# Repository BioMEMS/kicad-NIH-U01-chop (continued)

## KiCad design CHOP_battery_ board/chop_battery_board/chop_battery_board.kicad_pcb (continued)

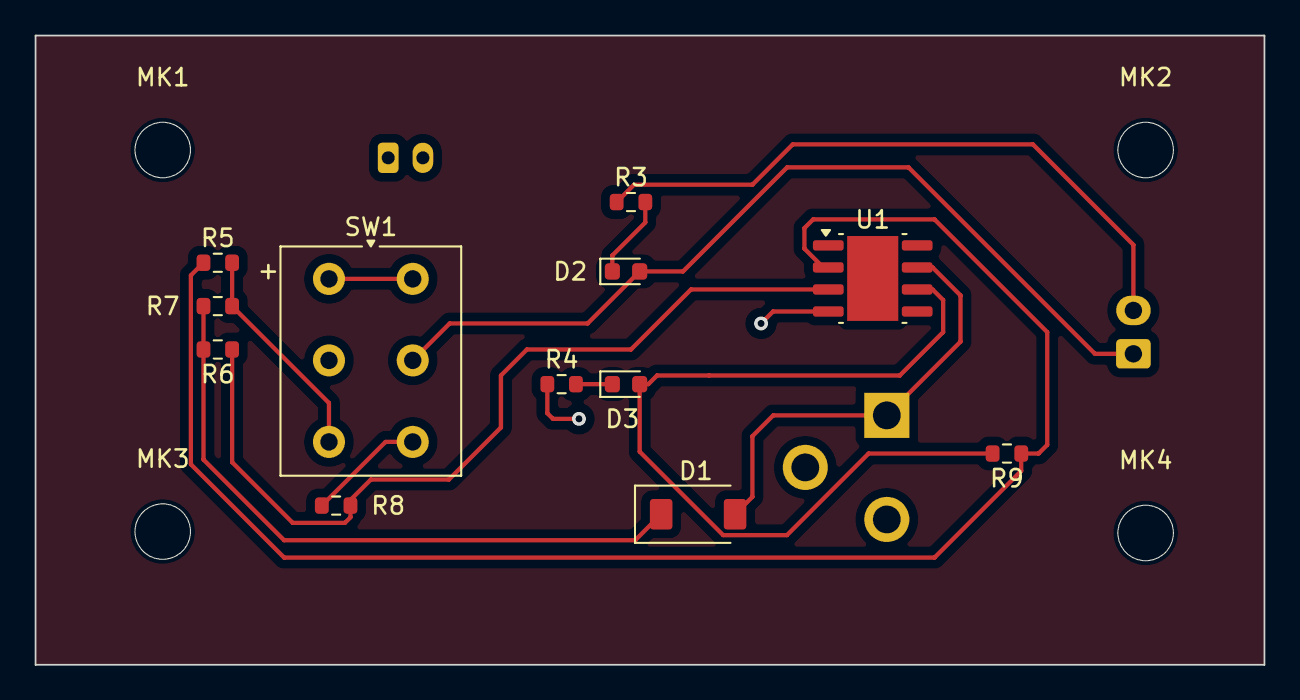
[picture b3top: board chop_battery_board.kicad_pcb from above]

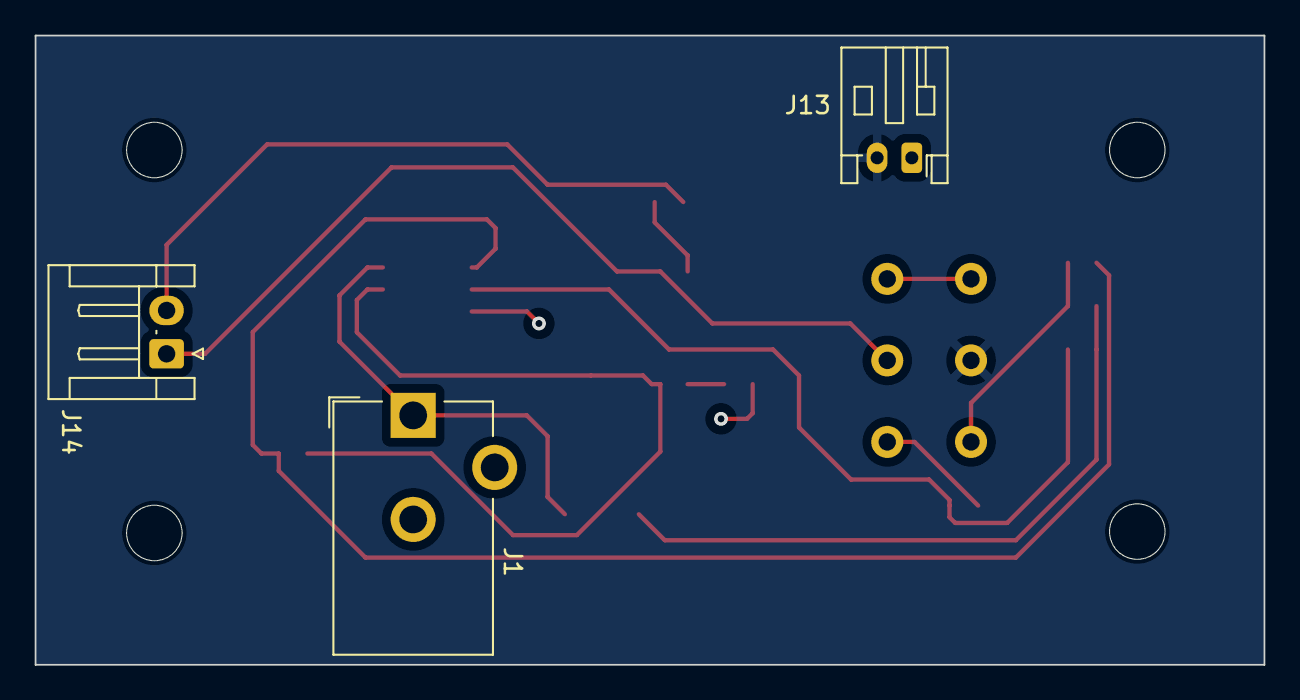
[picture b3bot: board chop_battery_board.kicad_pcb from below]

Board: 4 copper layers, 70.9 x 36.3 mm, 19 parts (3 on the bottom side), 12 nets.

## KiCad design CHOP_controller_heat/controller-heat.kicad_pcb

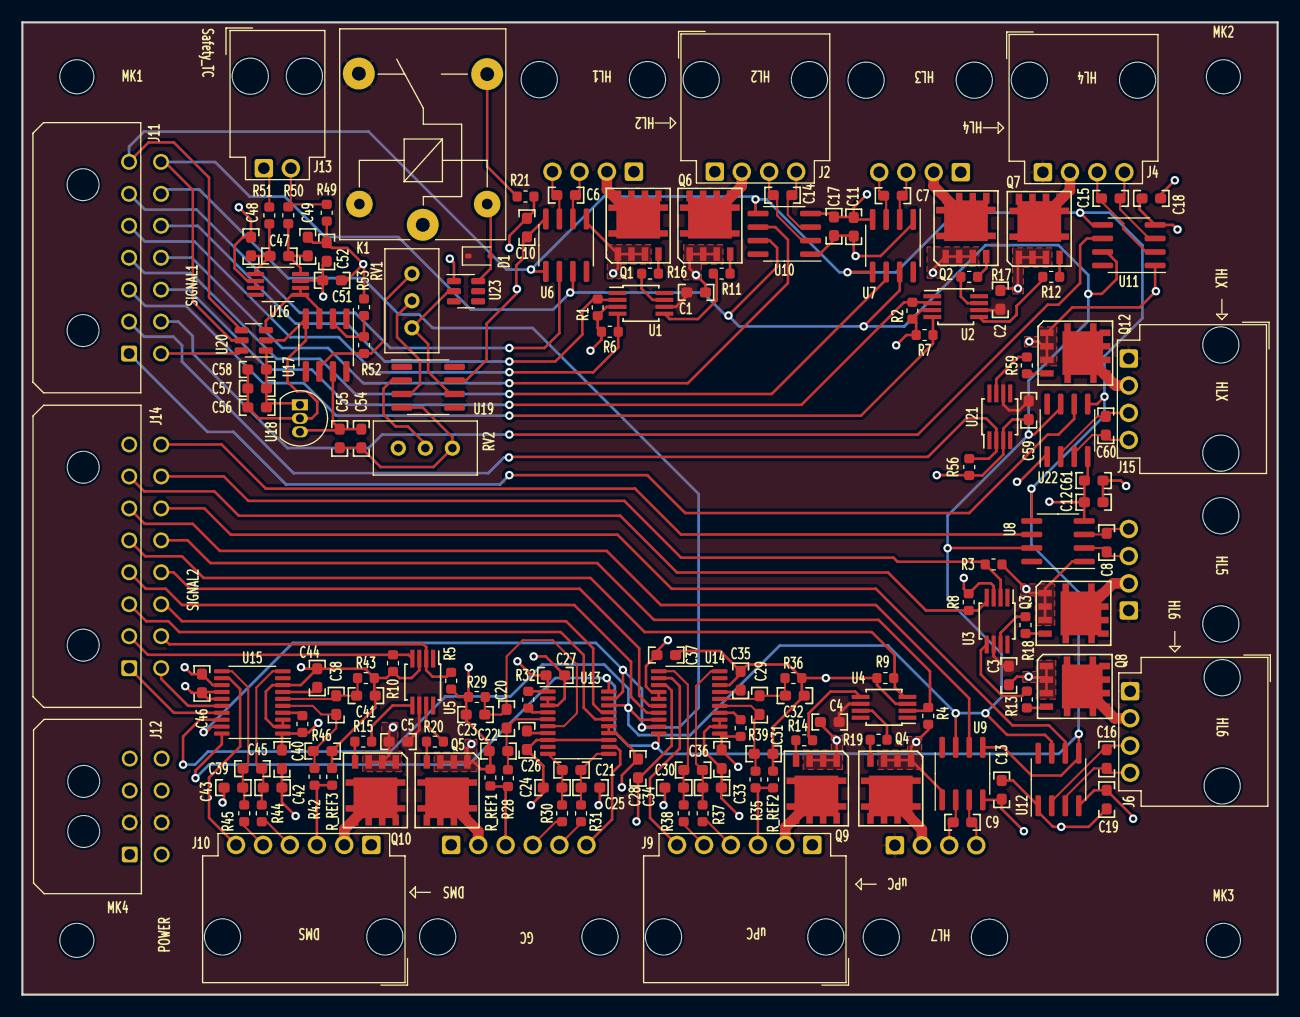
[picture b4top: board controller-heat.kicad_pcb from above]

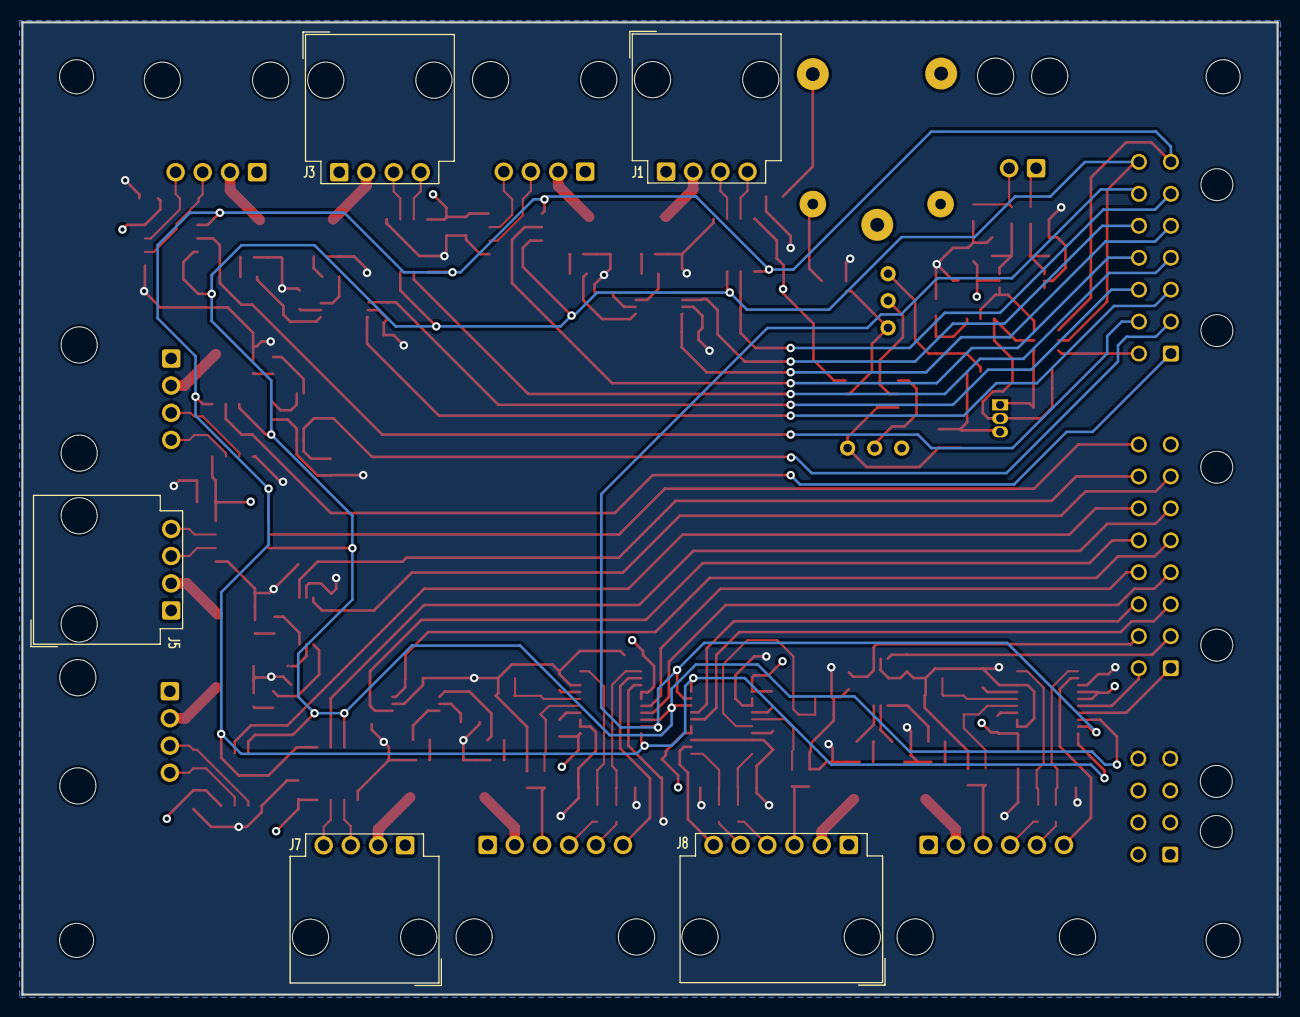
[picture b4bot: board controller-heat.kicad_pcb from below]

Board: 4 copper layers, 117.9 x 91.3 mm, 162 parts (5 on the bottom side), 126 nets.

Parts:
C1, C2, C3, C4, C5, C26, C35, C44, C59: 1u; C_0603_1608Metric_HandSolder
C6, C7, C8, C9, C14, C15, C16, C22, C23, C24, C25, C31, C32, C33, C34, C40, C41, C42, C43, C60: 10n; C_0603_1608Metric_HandSolder
C10, C11, C12, C13, C17, C18, C19, C20, C21, C27, C28, C29, C30, C36, C37, C38, C39, C45, C46, C61: 100n; C_0603_1608Metric_HandSolder
C47, C48, C49, C52, C54, C55: 10u; C_0603_1608Metric_HandSolder
C51, C56, C57, C58: 0.1u; C_0603_1608Metric_HandSolder
D1: BAT48JFILM; D_SOD-323
J1: HL1; Molex_SL_171975-0004_1x04_P2.54mm_Horizontal
J2: HL2; Molex_SL_171975-0004_1x04_P2.54mm_Horizontal
J3: HL3; Molex_SL_171975-0004_1x04_P2.54mm_Horizontal
J4: HL4; Molex_SL_171975-0004_1x04_P2.54mm_Horizontal
J5: HL5; Molex_SL_171975-0004_1x04_P2.54mm_Horizontal
J6: HL6; Molex_SL_171975-0004_1x04_P2.54mm_Horizontal
J7: HL7; Molex_SL_171975-0004_1x04_P2.54mm_Horizontal
J8: GC_RTD; Molex_SL_171975-0006_1x06_P2.54mm_Horizontal
J9: uPC_RTD; Molex_SL_171975-0006_1x06_P2.54mm_Horizontal
J10: DMS_RTD; Molex_SL_171975-0006_1x06_P2.54mm_Horizontal
J11: SIGNAL1; Molex_Micro-Fit_3.0_43045-1400_2x07_P3.00mm_Horizontal
J12: POWER; Molex_Micro-Fit_3.0_43045-0800_2x04_P3.00mm_Horizontal
J13: TC_SAFETY; Molex_SL_171975-0002_1x02_P2.54mm_Horizontal
J14: SIGNAL2; Molex_Micro-Fit_3.0_43045-1600_2x08_P3.00mm_Horizontal
J15: HLX; Molex_SL_171975-0004_1x04_P2.54mm_Horizontal
K1: J107F1CS1212VDC.36; Relay_SPDT_SANYOU_SRD_Series_Form_C
MK1, MK2, MK3, MK4: Mounting_Hole; MountingHole_3.2mm_M3
Q1, Q2, Q3, Q4, Q5, Q6, Q7, Q8, Q9, Q10, Q12: DMT6004LPS; PowerDI5060-8
R1, R2, R3, R4, R5, R6, R7, R8, R9, R10, R56: 4.7k; R_0603_1608Metric
R11, R12, R13, R14, R15, R16, R17, R18, R19, R20, R50, R51, R59: 100; R_0603_1608Metric
R21, R32, R39, R46: 10k; R_0603_1608Metric
R28, R29, R35, R36, R42, R43: 9.53k; R_0603_1608Metric
R30, R31, R37, R38, R44, R45: 10.5k; R_0603_1608Metric
R49: 1M; R_0603_1608Metric
R52: 9k; R_0603_1608Metric
R53: 1k; R_0603_1608Metric
RV1, RV2: 10k; Potentiometer_Bourns_3296W_Vertical
R_REF1, R_REF2, R_REF3: 2k; R_0603_1608Metric
U1, U2, U3, U4, U5, U21: TC4427; MSOP-8_3x3mm_P0.65mm_TI
U6, U7, U8, U9, U10, U11, U12, U22: MAX31855; SO-8_Maxim
U13, U14, U15: ADS1247; TSSOP-20_4.4x6.5mm_P0.65mm
U16: AD8497; MSOP-8_3x3mm_P0.65mm
U17, U19: LMC6081; SOIC-8_3.9x4.9mm_P1.27mm
U18: LP2950-3.3_TO92; TO-92_Inline
U20: ADC121S021; SOT-23-6
U23: NUD3124; SOT-23-6

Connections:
+3.3V: C10.1, C11.1, C12.1, C13.1, C17.1, C18.1, C19.1, C27.1, C28.1, C36.1, C37.1, C45.1, C46.1, C51.2, C52.2, C54.1, C55.1, C61.1, J12.3, J12.7, R32.1, R39.1, R46.1, RV2.1, U6.4 (VCC), U7.4 (VCC), U8.4 (VCC), U9.4 (VCC), U10.4 (VCC), U11.4 (VCC), U12.4 (VCC), U13.1 (DVDD), U13.14 (AVDD), U13.15 (Start), U14.1 (DVDD), U14.14 (AVDD), U14.15 (Start), U15.1 (DVDD), U15.14 (AVDD), U15.15 (Start), U16.7 (+Vs), U17.7 (V+), U18.3 (VI), U19.7 (V+), U22.4 (VCC)
+12V: C1.1, C2.1, C3.1, C4.1, C5.1, C59.1, D1.1 (K), J4.1, J5.1, J6.1, J7.1, J12.2, J12.6, J15.1, K1.4, K1.5, U1.6 (Vdd), U2.6 (Vdd), U3.6 (Vdd), U4.6 (Vdd), U5.6 (Vdd), U21.6 (Vdd)
+24V: J3.1, J8.1, J9.1, J10.1, J12.1, J12.5
/DMS_PWM_IN: J14.2, R10.1, U5.4 (IN_B)
/DMS_RTD+: J10.5, R45.2
/DMS_RTD++: J10.6, U15.12 (AIN3)
/DMS_RTD-: J10.4, R44.2
/DMS_RTD--: J10.3, R42.2, R_REF3.1
/DMS_RTD_CS: J14.9, U15.16 (N_CS)
/DMS_RTD_DRDY: J14.1, U15.17 (N_DRDY)
/GC_PWM_IN: J14.10, R5.1, U5.2 (IN_A)
/GC_RTD+: J8.5, R31.2
/GC_RTD++: J8.6, U13.12 (AIN3)
/GC_RTD-: J8.4, R30.2
/GC_RTD--: J8.3, R28.2, R_REF1.1
/GC_RTD_CS: J14.3, U13.16 (N_CS)
/GC_RTD_DRDY: J14.11, U13.17 (N_DRDY)
/HL1_CS: J11.6, U6.6 (N_CS)
/HL1_PWM_IN: J11.12, R1.1, U1.2 (IN_A)
/HL2_CS: J11.11, U10.6 (N_CS)
/HL2_PWM_IN: J11.5, R6.1, U1.4 (IN_B)
/HL3_CS: J11.4, U7.6 (N_CS)
/HL3_PWM_IN: J11.10, R2.1, U2.2 (IN_A)
/HL4_CS: J11.9, U11.6 (N_CS)
/HL4_PWM_IN: J11.3, R7.1, U2.4 (IN_B)
/HL5_CS: J14.16, U8.6 (N_CS)
/HL5_PWM_IN: J14.15, R3.1, U3.2 (IN_A)
/HL6_CS: J14.14, U12.6 (N_CS)
/HL6_PWM_IN: J14.7, R8.1, U3.4 (IN_B)
/HL7_CS: J14.6, U9.6 (N_CS)
/HL7_PWM_IN: J14.13, R4.1, U4.2 (IN_A)
/HLX_CS: J11.1, U22.6 (N_CS)
/HLX_PWM_IN: J11.2, R56.1, U21.2 (IN_A)
/MISO_1: J11.14, U6.7 (MISO), U7.7 (MISO), U8.7 (MISO), U9.7 (MISO), U10.7 (MISO), U11.7 (MISO), U12.7 (MISO), U13.18 (Dout), U14.18 (Dout), U15.18 (Dout), U20.5 (SDATA), U22.7 (MISO)
/MOSFET_DMS: J10.2, Q10.3 (D)
/MOSFET_GC: J8.2, Q5.3 (D)
/MOSFET_HL1: J1.2, Q1.3 (D)
/MOSFET_HL2: J2.2, Q6.3 (D)
/MOSFET_HL3: J3.2, Q2.3 (D)
/MOSFET_HL4: J4.2, Q7.3 (D)
/MOSFET_HL5: J5.2, Q3.3 (D)
/MOSFET_HL6: J6.2, Q8.3 (D)
/MOSFET_HL7: J7.2, Q4.3 (D)
/MOSFET_HLX: J15.2, Q12.3 (D)
/MOSFET_uPC: J9.2, Q9.3 (D)
/MOSI_1: J11.13, U13.19 (DIN), U14.19 (DIN), U15.19 (DIN)
/RTD Readout/DMS_RTD_N: C39.1, C42.2, R44.1, U15.10 (AIN1)
/RTD Readout/DMS_RTD_P: C39.2, C43.2, R45.1, U15.11 (AIN2)
/RTD Readout/DMS_Ref_N: C38.2, C41.1, R43.1, U15.6 (REFN0)
/RTD Readout/DMS_Ref_P: C38.1, C40.2, R42.1, U15.5 (REFP0)
/RTD Readout/GC_RTD_N: C21.1, C24.2, R30.1, U13.10 (AIN1)
/RTD Readout/GC_RTD_P: C21.2, C25.2, R31.1, U13.11 (AIN2)
/RTD Readout/GC_Ref_N: C20.2, C23.1, R29.1, U13.6 (REFN0)
/RTD Readout/GC_Ref_P: C20.1, C22.2, R28.1, U13.5 (REFP0)
/RTD Readout/uPC_RTD_N: C30.1, C33.2, R37.1, U14.10 (AIN1)
/RTD Readout/uPC_RTD_P: C30.2, C34.2, R38.1, U14.11 (AIN2)
/RTD Readout/uPC_Ref_N: C29.2, C32.1, R36.1, U14.6 (REFN0)
/RTD Readout/uPC_Ref_P: C29.1, C31.2, R35.1, U14.5 (REFP0)
/SAFETY_12V: J1.1, J2.1, K1.1
/SAFETY_CS: J11.8, U20.6 (CS)
/SCK_1: J11.7, U6.5 (SCK), U7.5 (SCK), U8.5 (SCK), U9.5 (SCK), U10.5 (SCK), U11.5 (SCK), U12.5 (SCK), U13.20 (SCLK), U14.20 (SCLK), U15.20 (SCLK), U20.4 (SCLK), U22.5 (SCK)
/Safet Cutoff/TC_SAFETY+: J13.2, R49.2, R50.2
/Safet Cutoff/TC_SAFETY-: J13.1, R51.1
/Safet Cutoff/V_CUTOFF: RV2.2, U19.2 (-)
/TC1+: C6.2, J1.4, U6.3 (T+)
/TC1-: C6.1, J1.3, U6.2 (T-)
/TC2+: C14.2, J2.4, U10.3 (T+)
/TC2-: C14.1, J2.3, U10.2 (T-)
/TC3+: C7.2, J3.4, U7.3 (T+)
/TC3-: C7.1, J3.3, U7.2 (T-)
/TC4+: C15.2, J4.4, U11.3 (T+)
/TC4-: C15.1, J4.3, U11.2 (T-)
/TC5+: C8.2, J5.4, U8.3 (T+)
/TC5-: C8.1, J5.3, U8.2 (T-)
/TC6+: C16.2, J6.4, U12.3 (T+)
/TC6-: C16.1, J6.3, U12.2 (T-)
/TC7+: C9.2, J7.4, U9.3 (T+)
/TC7-: C9.1, J7.3, U9.2 (T-)
/TCX+: C60.2, J15.4, U22.3 (T+)
/TCX-: C60.1, J15.3, U22.2 (T-)
/uPC_PWM_IN: J14.5, R9.1, U4.4 (IN_B)
/uPC_RTD+: J9.5, R38.2
/uPC_RTD++: J9.6, U14.12 (AIN3)
/uPC_RTD-: J9.4, R37.2
/uPC_RTD--: J9.3, R35.2, R_REF2.1
/uPC_RTD_CS: J14.12, U14.16 (N_CS)
/uPC_RTD_DRDY: J14.4, U14.17 (N_DRDY)
GNDREF: C1.2, C2.2, C3.2, C4.2, C5.2, C10.2, C11.2, C12.2, C13.2, C17.2, C18.2, C19.2, C22.1, C23.2, C24.1, C25.1, C26.1, C27.2, C28.2, C31.1, C32.2, C33.1, C34.1, C35.1, C36.2, C37.2, C40.1, C41.2, C42.1, C43.1, C44.1, C45.2, C46.2, C48.1, C49.2, C51.1, C52.1, C54.2, C55.2, C56.1, C57.1, C58.1, C59.2, C61.2, J12.4, J12.8, Q1.1 (S), Q2.1 (S), Q3.1 (S), Q4.1 (S), Q5.1 (S), Q6.1 (S), Q7.1 (S), Q8.1 (S), Q9.1 (S), Q10.1 (S), Q12.1 (S), R1.2, R2.2, R3.2, R4.2, R5.2, R6.2, R7.2, R8.2, R9.2, R10.2, R21.2, R29.2, R36.2, R43.2, R49.1, R53.2, R56.2, RV2.3, R_REF1.2, R_REF2.2, R_REF3.2, U1.3 (GND), U2.3 (GND), U3.3 (GND), U4.3 (GND), U5.3 (GND), U6.1 (GND), U7.1 (GND), U8.1 (GND), U9.1 (GND), U10.1 (GND), U11.1 (GND), U12.1 (GND), U13.2 (DGND), U13.3 (CLK), U13.8 (VREFCOM), U13.13 (AVSS), U14.2 (DGND), U14.3 (CLK), U14.8 (VREFCOM), U14.13 (AVSS), U15.2 (DGND), U15.3 (CLK), U15.8 (VREFCOM), U15.13 (AVSS), U16.2 (REF), U16.3 (-Vs), U17.4 (V-), U18.2 (GND), U19.4 (V-), U20.2 (GND), U21.3 (GND), U22.1 (GND), U23.1 (S1)
unnamed: D1.2 (A), K1.2, U23.6 (D1)
unnamed: K1.3, R21.1
unnamed: Q1.2 (G), R16.2
unnamed: Q2.2 (G), R17.2
unnamed: Q3.2 (G), R18.2
unnamed: Q4.2 (G), R19.2
unnamed: Q5.2 (G), R20.2
unnamed: Q6.2 (G), R11.1
unnamed: Q7.2 (G), R12.1
unnamed: Q8.2 (G), R13.1
unnamed: Q9.2 (G), R14.1
unnamed: Q10.2 (G), R15.1
unnamed: Q12.2 (G), R59.2
unnamed: R52.1, RV1.3, U17.6
unnamed: R16.1, U1.7 (OUT_A)
unnamed: R11.2, U1.5 (OUT_B)
unnamed: R17.1, U2.7 (OUT_A)
unnamed: R12.2, U2.5 (OUT_B)
unnamed: R18.1, U3.7 (OUT_A)
unnamed: R13.2, U3.5 (OUT_B)
unnamed: R19.1, U4.7 (OUT_A)
unnamed: R14.2, U4.5 (OUT_B)
unnamed: R20.1, U5.7 (OUT_A)
unnamed: R15.2, U5.5 (OUT_B)
unnamed: R32.2, U13.4 (N_Reset)
unnamed: C26.2, U13.7 (VREFOUT)
unnamed: R39.2, U14.4 (N_Reset)
unnamed: C35.2, U14.7 (VREFOUT)
unnamed: R46.2, U15.4 (N_Reset)
unnamed: C44.2, U15.7 (VREFOUT)
unnamed: C47.2, C49.1, R50.1, U16.8 (+IN)
unnamed: C47.1, C48.2, R51.2, U16.1 (-IN)
unnamed: U16.5 (SENSE), U16.6, U17.3 (+), U20.3 (Vin)
unnamed: R52.2, R53.1, U17.2 (-)
unnamed: C56.2, C57.2, C58.2, U18.1 (VO), U20.1 (VA)
unnamed: RV1.2, U19.3 (+)
unnamed: R59.1, U21.7 (OUT_A)
unnamed: RV1.1, U19.6, U23.2 (G1)

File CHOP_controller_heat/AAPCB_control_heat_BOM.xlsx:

Bill of Materials (BOM) - Heater Control Board
1. Reference Designators - Place all designators with the same part number in o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
2. Description Value Package - Advanced Assembly's system perfers this to be co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
3. Alternate Part Numbers - Place in additional columns to the right on the sam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
4. Do Not Install (DNI) Parts - Indicate quantity zero and/or add DNI column
5. Notes - Place in additional column on the same line
6. Refrain from using merged cells
7. Mfg - If you require a specific manufacturer, specify here
*Please contact your account executive with any questions.*
 |  |  |  | êAuto-populates as you fill in the previous cellsê
Mfg Part # | Description | Value | Pkg | Description Value Pkg *AAPCB Format* | Ref. Des. | Qty | DNI | Notes | Mfg (Optional) | Vendor (Optional) | Vendor Part # (Optional) | Alternate Mfg Part # (Optional) | Type (Optional)
CL10A105KA8NNNC | CAP CER | 1 µF 25V 10% | 0603 SMD | CAP CER 1 µF 25V 10% 0603 SMD | C1, C2, C3, C4, C5, C26, C35, C44, C59 | 9 |  |  | Samsung Electro-Mechanics | Digi-Key | 1276-1102-1-ND
C0603Y5V500-103ZNP-CT | CAP CER | 10000 pF 50V -20%, +80% | 0603 SMD | CAP CER 10000 pF 50V -20%, +80% 0603 SMD | C6, C7, C8, C9, C14, C15, C16, C22, C23, C24, C25, C31, C32, C33, C34, C40, C41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 | 20 |  |  | Venkel | Digi-Key | 2679-C0603Y5V500-103ZNP-CT-ND
CL10B104KB8NNNC | CAP CER | 0.1 µF 50V 10% | 0603 SMD | CAP CER 0.1 µF 50V 10% 0603 SMD | C10, C11, C12, C13, C17, C18, C19, C20, C21, C27, C28, C29, C30, C36, C37, C38,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 | 24 |  |  | Samsung Electro-Mechanics | Digi-Key | 1276-1000-1-ND
GRM188C81C106MA73D | CAP CER | 10 µF 16V 20% | 0603 SMD | CAP CER 10 µF 16V 20% 0603 SMD | C47, C48, C49, C52, C54, C55 | 6 |  |  | Murata Electronics | Digi-Key | 490-7198-1-ND
BAT48JFILM | DIODE SCHOTTKY | 40V 350mA | SOD-323 | DIODE SCHOTTKY 40V 350mA SOD-323 | D1 | 1 |  |  | STMicroelectronics | Digi-Key | 497-5711-1-ND
DMT6004LPS-13 | MOSFET N-Channel | 60V 22A | PowerDI5060-8 | MOSFET N-Channel 60V 22A PowerDI5060-8 | Q1, Q2, Q3, Q4, Q5, Q6, Q7, Q8, Q9, Q10, Q12 | 11 |  |  | Diodes Incorporated | Digi-Key | DMT6004LPS-13DICT-ND
RC0603FR-074K7L | RES | 4.7 kΩ 0.1W 1% | 0603 SMD | RES 4.7 kΩ 0.1W 1% 0603 SMD | R1, R2, R3, R4, R5, R6, R7, R8, R9, R10, R56 | 11 |  |  | YAGEO | Digi-Key | 311-4.70KHRCT-ND
RC0603FR-07100RL | RES | 100 Ω 0.1W 1% | 0603 SMD | RES 100 Ω 0.1W 1% 0603 SMD | R11, R12, R13, R14, R15, R16, R17, R18, R19, R20, R50, R51, R59 | 13 |  |  | YAGEO | Digi-Key | 311-100HRCT-ND
RC0603FR-0710KL | RES | 10 kΩ 0.1W 1% | 0603 SMD | RES 10 kΩ 0.1W 1% 0603 SMD | R21, R32, R39, R46 | 4 |  |  | YAGEO | Digi-Key | 311-10.0KHRCT-ND
RC0603FR-079K53L | RES | 9.53 kΩ 0.1W 1% | 0603 SMD | RES 9.53 kΩ 0.1W 1% 0603 SMD | R28, R29, R35, R36, R42, R43 | 6 |  |  | YAGEO | Digi-Key | 311-9.53KHRCT-ND
RMCF0603FT10K5 | RES | 10.5 kΩ 0.1W 1% | 0603 SMD | RES 10.5 kΩ 0.1W 1% 0603 SMD | R30, R31, R37, R38, R44, R45 | 6 |  |  | Stackpole Electronics Inc | Digi-Key | RMCF0603FT10K5CT-ND
RMCF0603FT1M00 | RES | 1 MΩ 0.1W 1% | 0603 SMD | RES 1 MΩ 0.1W 1% 0603 SMD | R49 | 1 |  |  | Stackpole Electronics Inc | Digi-Key | RMCF0603FT1M00CT-ND
RC0603FR-079K09L | RES | 9.09 kΩ 0.1W 1% | 0603 SMD | RES 9.09 kΩ 0.1W 1% 0603 SMD | R52 | 1 |  |  | YAGEO | Digi-Key | 311-9.09KHRCT-ND
RC0603FR-071KL | RES | 1 kΩ 0.1W 1% | 0603 SMD | RES 1 kΩ 0.1W 1% 0603 SMD | R53 | 1 |  |  | YAGEO | Digi-Key | 311-1.00KHRCT-ND
RC0603JR-072KL | RES | 2 kΩ 0.1W 5% | 0603 SMD | RES 2 kΩ 0.1W 5% 0603 SMD | R_REF1, R_REF2, R_REF3 | 3 |  |  | YAGEO | Digi-Key | 311-2.0KGRCT-ND
TC4427VUA713 | Low-Side Gate Driver IC Non-Inverting | 1.5A | 8-MSOP | Low-Side Gate Driver IC Non-Inverting 1.5A 8-MSOP | U1, U2, U3, U4, U5, U21 | 6 |  |  | Microchip Technology | Digi-Key | TC4427VUA713CT-ND
MAX31855KASA+T | IC CONV THERMOCOUPLE-DGTL SOIC | 14 bit SPI | 8-SOIC | IC CONV THERMOCOUPLE-DGTL SOIC 14 bit SPI 8-SOIC | U6, U7, U8, U9, U10, U11, U12, U22 | 8 |  |  | Analog Devices Inc./Maxim Integrated | Digi-Key | MAX31855KASA+TCT-ND
ADS1247IPW | Analog to Digital Converter 2, 3 Input 1 Sigma-Delta | 24 bit SPI | 20-TSSOP | Analog to Digital Converter 2, 3 Input 1 Sigma-Delta 24 bit SPI 20-TSSOP | U13, U14, U15 | 3 |  |  | Texas Instruments | Digi-Key | 296-24293-5-ND
AD8497ARMZ | IC THERMOCOUPLE A W/COMP | Differential Analog | 8-MSOP | IC THERMOCOUPLE A W/COMP Differential Analog 8-MSOP | U16 | 1 |  |  | Analog Devices Inc. | Digi-Key | 505-AD8497ARMZ-ND
LMC6081AIMX/NOPB | General Purpose Amplifier 1 Circuit Rail-to-Rail 8-SOIC | 1.3MHz | 8-SOIC | General Purpose Amplifier 1 Circuit Rail-to-Rail 8-SOIC 1.3MHz 8-SOIC | U17, U19 | 2 |  |  | Texas Instruments | Digi-Key | 296-35439-1-ND
ADC121S021CIMFX/NOPB | Analog to Digital Converter 1 Input 1 SAR | 12 bit SPI | SOT-23-6 | Analog to Digital Converter 1 Input 1 SAR 12 bit SPI SOT-23-6 | U20 | 1 |  |  | Texas Instruments | Digi-Key | 296-37316-1-ND
NUD3124DMT1G | Gate Drivers 28V Industrial Relay Inductive Load | 28V 150mA | SC-74 | Gate Drivers 28V Industrial Relay Inductive Load 28V 150mA SC-74 | U23 | 1 |  |  | onsemi | Mouser | NUD3124DMT1GOSTR-ND

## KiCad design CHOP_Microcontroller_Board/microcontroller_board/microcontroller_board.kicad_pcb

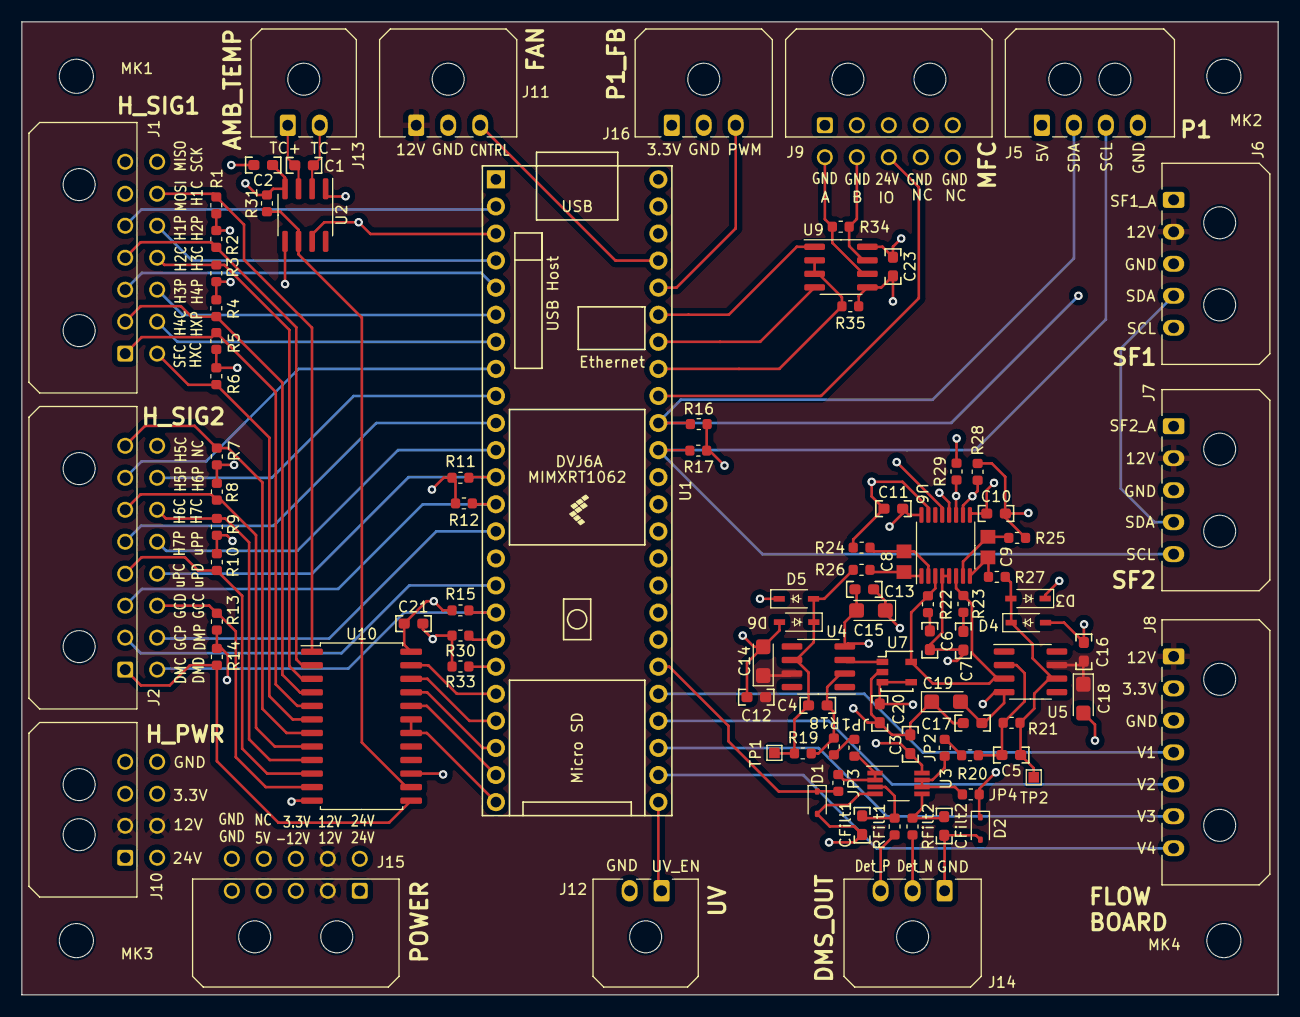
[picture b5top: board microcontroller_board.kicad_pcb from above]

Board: 4 copper layers, 117.9 x 91.3 mm, 99 parts (0 on the bottom side), 83 nets.

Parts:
C1: 10n; C_0603_1608Metric_HandSolder
C2, C3, C20: 100n; C_0603_1608Metric_HandSolder
C4, C5, C12, C13, C16, C17, C23: 0.1u; C_0603_1608Metric_HandSolder
C6, C7, C10, C11, C21: 10u; C_0603_1608Metric_HandSolder
C8, C9: 8.2n; C_0805_2012Metric_Pad1.29x1.40mm_HandSolder
C14, C15, C18, C19: 6.8u; CP_EIA-3216-18_Kemet-A
CFilt1, CFilt2: 100n; C_0603_1608Metric_HandSolder
D1, D2: MM3Z3V0T1G; D_SOD-323
D3, D4, D5, D6: BAT48; D_SOD-323_STMicroelectronics
J1: HEATER_SIGNAL_1; Molex_Micro-Fit_3.0_43045-1400_2x07_P3.00mm_Horizontal
J2: HEATER_SIGNAL_2; Molex_Micro-Fit_3.0_43045-1600_2x08_P3.00mm_Horizontal
J5: P1; Molex_Micro-Fit_3.0_43650-0400_1x04_P3.00mm_Horizontal
J6: SF1; Molex_Micro-Fit_3.0_43650-0500_1x05_P3.00mm_Horizontal
J7: SF2; Molex_Micro-Fit_3.0_43650-0500_1x05_P3.00mm_Horizontal
J8: Flow Control Board; Molex_Micro-Fit_3.0_43650-0700_1x07_P3.00mm_Horizontal
J9: MFC; Molex_Micro-Fit_3.0_43045-1000_2x05_P3.00mm_Horizontal
J10: POWER_HEAT; Molex_Micro-Fit_3.0_43045-0800_2x04_P3.00mm_Horizontal
J11: Fan; Molex_Micro-Fit_3.0_43650-0300_1x03_P3.00mm_Horizontal
J12: HVPS; Molex_Micro-Fit_3.0_43650-0200_1x02_P3.00mm_Horizontal
J13: AMBIENT_TEMP; Molex_Micro-Fit_3.0_43650-0200_1x02_P3.00mm_Horizontal
J14: DMS_Output; Molex_Micro-Fit_3.0_43650-0300_1x03_P3.00mm_Horizontal
J15: Power_IN; Molex_Micro-Fit_3.0_43045-1000_2x05_P3.00mm_Horizontal
J16: P1_FB; Molex_Micro-Fit_3.0_43650-0300_1x03_P3.00mm_Horizontal
JP1, JP2, JP3, JP4: SJ_2_Open; R_0603_1608Metric
MK1, MK2, MK3, MK4: Mounting_Hole; MountingHole_3.2mm_M3
R1, R2, R3, R4, R5, R6, R7, R8, R9, R10, R11, R12, R13, R14, R15, R16, R17, R29, R30, R31, R33: 4.7k; R_0603_1608Metric
R18, R19, R20, R21: 1k; R_0603_1608Metric
R22, R23: 0.1; R_0603_1608Metric
R24, R25, R26, R27: 10; R_0603_1608Metric
R28: 10k; R_0603_1608Metric
R34: 220; R_0603_1608Metric
R35: 330; R_0603_1608Metric
RFilt1, RFilt2: 1k; R_0603_1608Metric
TP1: Det_P_TP; TestPoint_Pad_1.0x1.0mm
TP2: Det_N_TP; TestPoint_Pad_1.0x1.0mm
U1: Teensy4.1_Mounted; Teensy41_Mounted
U2: MAX31855; SO-8_Maxim
U3: TLV2333; VSSOP-8_3.0x3.0mm_P0.65mm
U4, U5: THS4031; SOIC-8_3.9x4.9mm_P1.27mm
U6: ADS8353_TSSOP-16; TSSOP-16_4.4x5mm_P0.65mm
U7: Ref2025; SOT23-5_Ref2025
U9: SP3485CN; SOIC-8_3.9x4.9mm_P1.27mm
U10: CD74HC154; SOIC-24W_7.5x15.4mm_P1.27mm

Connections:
1p25VRef: U4.3 (+), U7.1 (VBias)
2p5VRef: R22.1, R23.1, U5.3 (+), U6.3 (REFIO_A), U6.6 (REFIO_B), U7.5 (VRef)
+3.3V: C2.1, C10.1, C20.2, C21.2, C23.2, J8.2, J10.3, J10.7, J15.8, J16.1, R1.2, R2.2, R3.2, R4.2, R5.2, R6.2, R7.2, R8.2, R9.2, R10.2, R11.2, R12.2, R13.2, R14.2, R15.2, R16.2, R17.2, R29.1, R31.2, U2.4 (VCC), U6.9 (DVDD), U7.3 (EN), U7.4 (VIN), U9.8 (VCC), U10.24 (VCC)
+5V: C3.1, C11.2, D3.1 (K), D5.1 (K), J5.1, J15.4, U1.48 (VIN), U3.8 (V+), U6.16 (AVDD)
+12V: C12.1, C14.1, C16.1, C18.1, J6.2, J7.2, J8.1, J10.2, J10.6, J11.1, J15.2, J15.7, U4.7 (V+), U5.7 (V+)
+24V: J9.3, J10.1, J10.5, J15.1, J15.6
-12V: C13.1, C15.2, C17.1, C19.2, J15.3, U4.4 (V-), U5.4 (V-)
/AMBIENT TEMP/TCA+: C1.2, J13.1, U2.3 (T+)
/AMBIENT TEMP/TCA-: C1.1, J13.2, U2.2 (T-)
/AMBIENT_CS: R31.1, U2.6 (N_CS), U10.14 (Y12)
/ANALOG_SF1: J6.1, U1.33 (41_A17)
/ANALOG_SF2: J7.1, U1.32 (40_A16)
/CS_0: U1.20 (28_RX7), U10.23 (A0)
/CS_1: U1.21 (29_TX7), U10.22 (A1)
/CS_2: U1.22 (30_CRX3), U10.21 (A2)
/CS_3: U1.23 (31_CTX3), U10.20 (A3)
/CS_EN: U1.24 (32_OUT1B), U10.18 (E1), U10.19 (E2)
/DMS SIGNAL/Det_Signal_ADC/Det_Neg_Signal: JP2.2 (B), R20.2
/DMS SIGNAL/Det_Signal_ADC/Det_Pos_Signal: JP1.2 (B), R18.2
/DMS SIGNAL/Detect_Neg: JP2.1 (A), JP4.1 (A), U3.6 (-), U3.7
/DMS SIGNAL/Detect_Neg_Unfiltered: J14.2, RFilt2.1
/DMS SIGNAL/Detect_Pos: JP1.1 (A), JP3.1 (A), U3.1, U3.2 (-)
/DMS SIGNAL/Detect_Pos_Unfiltered: J14.3, RFilt1.1
/DMS_PWM_IN: J2.10, U1.14 (12_MISO_MQSL)
/DMS_RTD_CS: J2.1, R14.1, U10.13 (Y11)
/DMS_RTD_DRDY: J2.9, R15.1, U1.17 (25_A11_RX6_SDA2)
/Det_ADC_CS: R29.2, U6.11 (N_CS), U10.15 (Y13)
/Det_Neg_ARead: D2.1 (K), JP4.2 (B), U1.31 (39_MISO1_OUT1A)
/Det_Pos_ARead: D1.1 (K), JP3.2 (B), U1.30 (38_CS1_IN1)
/FAN_CONTROL: J11.3, U1.45 (23_A9_CRX1_MCLK1)
/GC_PWM_IN: J2.2, U1.16 (24_A10_TX6_SCL2)
/GC_RTD_CS: J2.11, R13.1, U10.11 (Y10)
/GC_RTD_DRDY: J2.3, R12.1, U1.13 (11_MOSI_CTX1)
/HL1_CS: J1.13, R1.1, U10.1 (Y0)
/HL1_PWM_IN: J1.5, U1.2 (0_RX1_CRX2_CS1)
/HL2_CS: J1.4, R2.1, U10.2 (Y1)
/HL2_PWM_IN: J1.12, U1.4 (2_OUT2)
/HL3_CS: J1.11, R3.1, U10.3 (Y2)
/HL3_PWM_IN: J1.3, U1.5 (3_LRCLK2)
/HL4_CS: J1.2, R4.1, U10.4 (Y3)
/HL4_PWM_IN: J1.10, U1.6 (4_BCLK2)
/HL5_CS: J2.8, R7.1, U10.7 (Y6)
/HL5_PWM_IN: J2.7, U1.8 (6_OUT1D)
/HL6_CS: J2.6, R8.1, U10.8 (Y7)
/HL6_PWM_IN: J2.15, U1.9 (7_RX2_OUT1A)
/HL7_CS: J2.14, R9.1, U10.9 (Y8)
/HL7_PWM_IN: J2.5, U1.10 (8_TX2_IN1)
/HLX_CS: J1.8, R6.1, U10.6 (Y5)
/HLX_PWM_IN: J1.9, U1.7 (5_IN2)
/MFC/MFC_A: J9.6, R34.1, U9.6 (A)
/MFC/MFC_B: J9.7, R34.2, U9.7 (B)
/MFC_IO_LINK: J9.8, U1.40 (18_A4_SDA)
/MFC_RTS: R35.1, U1.41 (19_A5_SCL), U9.2 (~RE), U9.3 (DE)
/MFC_RX: U1.43 (21_A7_RX5_BCLK1), U9.1 (RO)
/MFC_TX: U1.42 (20_A6_TX5_LRCLK1), U9.4 (DI)
/MISO_1: J1.7, U1.3 (1_TX1_CTX2_MISO1), U2.7 (MISO), U6.13 (SDO_A)
/MOSI_1: J1.6, R28.2, R30.1, U1.18 (26_A12_MOSI1), U6.10 (SDI)
/P1_PWM_IN: J16.3, U1.44 (22_A8_CTX1)
/SAFETY_CS: J1.1, R5.1, U10.5 (Y4)
/SCK_1: J1.14, R33.1, U1.19 (27_A13_SCK1), U2.5 (SCK), U6.12 (SCLK)
/SCL1: J5.3, J6.5, J7.5, R17.1, U1.38 (16_A2_RX4_SCL1)
/SDA1: J5.2, J6.4, J7.4, R16.1, U1.39 (17_A3_TX4_SDA1)
/UV_EN: J12.1, U1.25 (33_MCLK2)
/VALVE1: J8.4, U1.29 (37_CS)
/VALVE2: J8.5, U1.28 (36_CS)
/VALVE3: J8.6, U1.27 (35_TX8)
/VALVE4: J8.7, U1.26 (34_RX8)
/uPC_PWM_IN: J2.13, U1.11 (9_OUT1C)
/uPC_RTD_CS: J2.4, R10.1, U10.10 (Y9)
/uPC_RTD_DRDY: J2.12, R11.1, U1.12 (10_CS_MQSR)
GNDREF: C2.2, C3.2, C6.2, C7.2, C10.2, C11.1, C12.2, C13.2, C14.2, C15.1, C16.2, C17.2, C18.2, C19.1, C20.1, C21.1, C23.1, CFilt1.2, CFilt2.1, D1.2 (A), D2.2 (A), D4.2 (A), D6.2 (A), J5.4, J6.3, J7.3, J8.3, J9.1, J9.2, J9.4, J9.5, J10.4, J10.8, J11.2, J12.2, J14.1, J15.5, J15.10, J16.2, R24.2, R25.1, R28.1, R30.2, R33.2, R35.2, U1.1 (GND), U1.34 (GND), U1.47 (GND), U2.1 (GND), U3.4 (V-), U6.4 (REFGND_A), U6.5 (REFGND_B), U6.15 (GND), U7.2 (GND), U9.5 (GND), U10.12 (GND)
unnamed: C6.1, R22.2
unnamed: C7.1, R23.2
unnamed: C5.2, D3.2 (A), D4.1 (K), R21.1, R27.1, TP2.1, U5.6
unnamed: C4.1, D5.2 (A), D6.1 (K), R19.1, R26.1, TP1.1, U4.6
unnamed: CFilt1.1, RFilt1.2, U3.3 (+)
unnamed: CFilt2.2, RFilt2.2, U3.5 (+)
unnamed: C4.2, R18.1, R19.2, U4.2 (-)
unnamed: C5.1, R20.1, R21.2, U5.2 (-)
unnamed: C8.2, R24.1, U6.2 (AINM_A)
unnamed: C9.2, R25.2, U6.7 (AINM_B)
unnamed: C8.1, R26.2, U6.1 (AINP_A)
unnamed: C9.1, R27.2, U6.8 (AINP_B)

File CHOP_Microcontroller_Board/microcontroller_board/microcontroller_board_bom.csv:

#,Reference,Qty/Board,Value,Footprint,DNP,Part #,Total Q w/ overage,Vendor,Description
1,C1,1,10n,NYSEARCH:C_0603_1608Metric_HandSolder,FALSE,GRT1885C1E103FA02D,5,digikey,"10000 pF ±1% 25V Ceramic Capacitor C0G, NP0 0603 (1608 Metric)"
2,"C2, C3, C20, CFilt1, CFilt2",5,100n,NYSEARCH:C_0603_1608Metric_HandSolder,FALSE,KGM15BR71H104JT,25,digikey,0.1 µF ±5% 50V Ceramic Capacitor X7R 0603 (1608 Metric)
3,"C4, C5, C12, C13, C16, C17, C23",7,0.1u,NYSEARCH:C_0603_1608Metric_HandSolder,FALSE,KGM15BR71H104JT,35,digikey,0.1 µF ±5% 50V Ceramic Capacitor X7R 0603 (1608 Metric)
4,"C6, C7, C10, C11, C21",5,10u,NYSEARCH:C_0603_1608Metric_HandSolder,FALSE,GRM188R61A106KE69D,25,digikey,10 µF ±10% 10V Ceramic Capacitor X5R 0603 (1608 Metric)
5,"C8, C9",2,8.2n,Capacitor_SMD:C_0805_2012Metric_Pad1.29x1.40mm_HandSolder,FALSE,CGA3E2C0G1H822J080AE,10,digikey,"8200 pF ±5% 50V Ceramic Capacitor C0G, NP0 0603 (1608 Metric)"
6,"C14, C15, C18, C19",4,6.8u,Capacitor_Tantalum_SMD:CP_EIA-3216-18_Kemet-A,FALSE,T498A685K016ATE2K6,20,digikey,6.8 µF Molded Tantalum Capacitors 16 V 1206 (3216 Metric) 2.6Ohm
7,"D1, D2",2,MM3Z3V0T1G,Diode_SMD:D_SOD-323,FALSE,MM3Z3V0T1G,10,digikey,Zener Diode 3 V 300 mW ±7% Surface Mount SOD-323
8,"D3, D4, D5, D6",4,BAT48,NYSEARCH:D_SOD-323_STMicroelectronics,FALSE,SD103AWS-HE3-18,20,digikey,Diode 40 V 350mA Surface Mount SOD-323
9,J1,1,HEATER_SIGNAL_1,Connector_Molex:Molex_Micro-Fit_3.0_43045-1400_2x07_P3.00mm_Horizontal,FALSE,0430451400,5,digikey,"Connector Header Through Hole, Right Angle 14 position 0.118"" (3.00mm)"
10,J2,1,HEATER_SIGNAL_2,Connector_Molex:Molex_Micro-Fit_3.0_43045-1600_2x08_P3.00mm_Horizontal,FALSE,0430451600,5,digikey,"Connector Header Through Hole, Right Angle 16 position 0.118"" (3.00mm)"
11,J5,1,P1,Connector_Molex:Molex_Micro-Fit_3.0_43650-0400_1x04_P3.00mm_Horizontal,FALSE,0436500400,5,digikey,"Connector Header Through Hole, Right Angle 4 position 0.118"" (3.00mm)"
12,J6,1,SF1,Connector_Molex:Molex_Micro-Fit_3.0_43650-0500_1x05_P3.00mm_Horizontal,FALSE,0436500500,5,digikey,"Connector Header Through Hole, Right Angle 5 position 0.118"" (3.00mm)"
13,J7,1,SF2,Connector_Molex:Molex_Micro-Fit_3.0_43650-0500_1x05_P3.00mm_Horizontal,FALSE,0436500500,5,digikey,"Connector Header Through Hole, Right Angle 5 position 0.118"" (3.00mm)"
14,J8,1,Flow Control Board,Connector_Molex:Molex_Micro-Fit_3.0_43650-0700_1x07_P3.00mm_Horizontal,FALSE,0436500700,5,digikey,"Connector Header Through Hole, Right Angle 7 position 0.118"" (3.00mm)"
15,J9,1,MFC,Connector_Molex:Molex_Micro-Fit_3.0_43045-1000_2x05_P3.00mm_Horizontal,FALSE,0430451000,5,digikey,"Connector Header Through Hole, Right Angle 10 position 0.118"" (3.00mm)"
16,J10,1,POWER_HEAT,Connector_Molex:Molex_Micro-Fit_3.0_43045-0800_2x04_P3.00mm_Horizontal,FALSE,0430450800,5,digikey,"Connector Header Through Hole, Right Angle 8 position 0.118"" (3.00mm)"
17,J11,1,Fan,Connector_Molex:Molex_Micro-Fit_3.0_43650-0300_1x03_P3.00mm_Horizontal,FALSE,0436500300,5,digikey,"Connector Header Through Hole, Right Angle 3 position 0.118"" (3.00mm)"
18,J12,1,HVPS,Connector_Molex:Molex_Micro-Fit_3.0_43650-0200_1x02_P3.00mm_Horizontal,FALSE,0436500200,5,digikey,"Connector Header Through Hole, Right Angle 2 position 0.118"" (3.00mm)"
19,J13,1,AMBIENT_TEMP,Connector_Molex:Molex_Micro-Fit_3.0_43650-0200_1x02_P3.00mm_Horizontal,FALSE,0436500200,5,digikey,"Connector Header Through Hole, Right Angle 2 position 0.118"" (3.00mm)"
20,J14,1,DMS_Output,Connector_Molex:Molex_Micro-Fit_3.0_43650-0300_1x03_P3.00mm_Horizontal,FALSE,0436500300,5,digikey,"Connector Header Through Hole, Right Angle 3 position 0.118"" (3.00mm)"
21,J15,1,Power_IN,NYSEARCH:Molex_Micro-Fit_3.0_43045-1000_2x05_P3.00mm_Horizontal,FALSE,0430451000,5,digikey,"Connector Header Through Hole, Right Angle 10 position 0.118"" (3.00mm)"
22,J16,1,P1_FB,Connector_Molex:Molex_Micro-Fit_3.0_43650-0300_1x03_P3.00mm_Horizontal,FALSE,0436500300,5,digikey,"Connector Header Through Hole, Right Angle 3 position 0.118"" (3.00mm)"
23,"JP1, JP2, JP3, JP4",4,SJ_2_Open,NYSEARCH:R_0603_1608Metric,FALSE,CRCW06030000Z0EAHP,20,digikey,"0 Ohms Jumper Chip Resistor 0603 (1608 Metric) Automotive AEC-Q200, Pulse Withstanding Thick Film"
24,"MK1, MK2, MK3, MK4",4,Mounting_Hole,MountingHole:MountingHole_3.2mm_M3,TRUE,,0,,
25,"R1, R2, R3, R4, R5, R6, R7, R8, R9, R10, R11, R12, R13, R14, R15, R16, R17, R29, R30, R31, R33",21,4.7k,NYSEARCH:R_0603_1608Metric,FALSE,RMCF0603FT4K70,105,digikey,"4.7 kOhms ±1% 0.1W, 1/10W Chip Resistor 0603 (1608 Metric) Automotive AEC-Q200 Thick Film"
26,"R18, R19, R20, R21, RFilt1, RFilt2",6,1k,NYSEARCH:R_0603_1608Metric,FALSE,RMCF0603FT1K00,30,digikey,"1 kOhms ±1% 0.1W, 1/10W Chip Resistor 0603 (1608 Metric) Automotive AEC-Q200 Thick Film"
27,"R22, R23",2,0.1,NYSEARCH:R_0603_1608Metric,FALSE,CRL0603-FW-R100ELF,10,digikey,"100 mOhms ±1% 0.125W, 1/8W Chip Resistor 0603 (1608 Metric) Thick Film"
28,"R24, R25, R26, R27",4,10,NYSEARCH:R_0603_1608Metric,FALSE,RMCF0603FT10R0,20,digikey,"10 Ohms ±1% 0.1W, 1/10W Chip Resistor 0603 (1608 Metric) Automotive AEC-Q200 Thick Film"
29,R28,1,10k,NYSEARCH:R_0603_1608Metric,FALSE,RMCF0603FT10K0,5,digikey,"10 kOhms ±1% 0.1W, 1/10W Chip Resistor 0603 (1608 Metric) Automotive AEC-Q200 Thick Film"
30,R34,1,220,NYSEARCH:R_0603_1608Metric,FALSE,RC0603JR-13220RL,5,digikey,"220 Ohms ±5% 0.1W, 1/10W Chip Resistor 0603 (1608 Metric) Moisture Resistant Thick Film"
31,R35,1,330,NYSEARCH:R_0603_1608Metric,FALSE,CR0603-JW-331ELF,5,digikey,"330 Ohms ±5% 0.1W, 1/10W Chip Resistor 0603 (1608 Metric) Moisture Resistant Thick Film"
32,TP1,1,Det_P_TP,TestPoint:TestPoint_Pad_1.0x1.0mm,TRUE,,0,,
33,TP2,1,Det_N_TP,TestPoint:TestPoint_Pad_1.0x1.0mm,TRUE,,0,,
34,U1,1,Teensy4.1_Mounted,NIH-SCENT:Teensy41_Mounted,FALSE,DEV-16771,5,digikey,RT1062 Teensy 4.1 i.MX ARM® Cortex®-M7 MPU Embedded Evaluation Board
35,U2,1,MAX31855,NYSEARCH:SO-8_Maxim,FALSE,MAX31855KASA+T,5,digikey,IC CONV THERMOCOUPLE-DGTL SOIC
36,U3,1,TLV2333,Package_SO:VSSOP-8_3.0x3.0mm_P0.65mm,FALSE,TLV2333IDGKT,5,digikey,Zero-Drift Amplifier 2 Circuit Rail-to-Rail 8-VSSOP
37,"U4, U5",2,THS4031,Package_SO:SOIC-8_3.9x4.9mm_P1.27mm,FALSE,THS4031CDR,10,digikey,Voltage Feedback Amplifier 1 Circuit 8-SOIC
38,U6,1,ADS8353_TSSOP-16,Package_SO:TSSOP-16_4.4x5mm_P0.65mm,FALSE,ADS8353IPWR,5,digikey,16 Bit Analog to Digital Converter 2 Input 2 SAR 16-TSSOP
39,U7,1,Ref2025,NYSEARCH:SOT23-5_Ref2025,FALSE,REF2025AIDDCR,5,digikey,"Series Voltage Reference IC Fixed 1.24V, 2.5V V ±0.05% 20 mA SOT-23-THIN"
40,U9,1,SP3485CN,Package_SO:SOIC-8_3.9x4.9mm_P1.27mm,FALSE,SP3485CN-L/TR,5,digikey,"1/1 Transceiver Half RS422, RS485 8-SOIC"
41,U10,1,CD74HC154,Package_SO:SOIC-24W_7.5x15.4mm_P1.27mm,FALSE,CD74HC154M96,5,digikey,Decoder/Demultiplexer 1 x 4:16 24-SOIC
42,Board,4,n/a,n/a,n/a,n/a,n/a,JLC,
43,"pin_socket1, pin_socket2",2,,Connector_PinSocket_2.54mm:PinSocket_1x24_P2.54mm_Vertical,FALSE,PPPC241LFBN-RC,10,digikey,"24 Position Header Connector 0.100"" (2.54mm) Through Hole Gold"

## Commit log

2025-05-21 Setup chop repository
2025-05-24 PCB Final 5/24
2025-05-28 PCB update 5/27
2025-05-29 controller heat 3d
2025-05-31 CHOP 3d models 5/30
2025-05-31 CHOP MCU step
2025-05-31 CHOP MCU update OLED
2025-05-31 CHOP MCU update step
2025-06-04 Battery board edit
2025-06-05 Gerber files
2025-06-05 Gerber files 2
